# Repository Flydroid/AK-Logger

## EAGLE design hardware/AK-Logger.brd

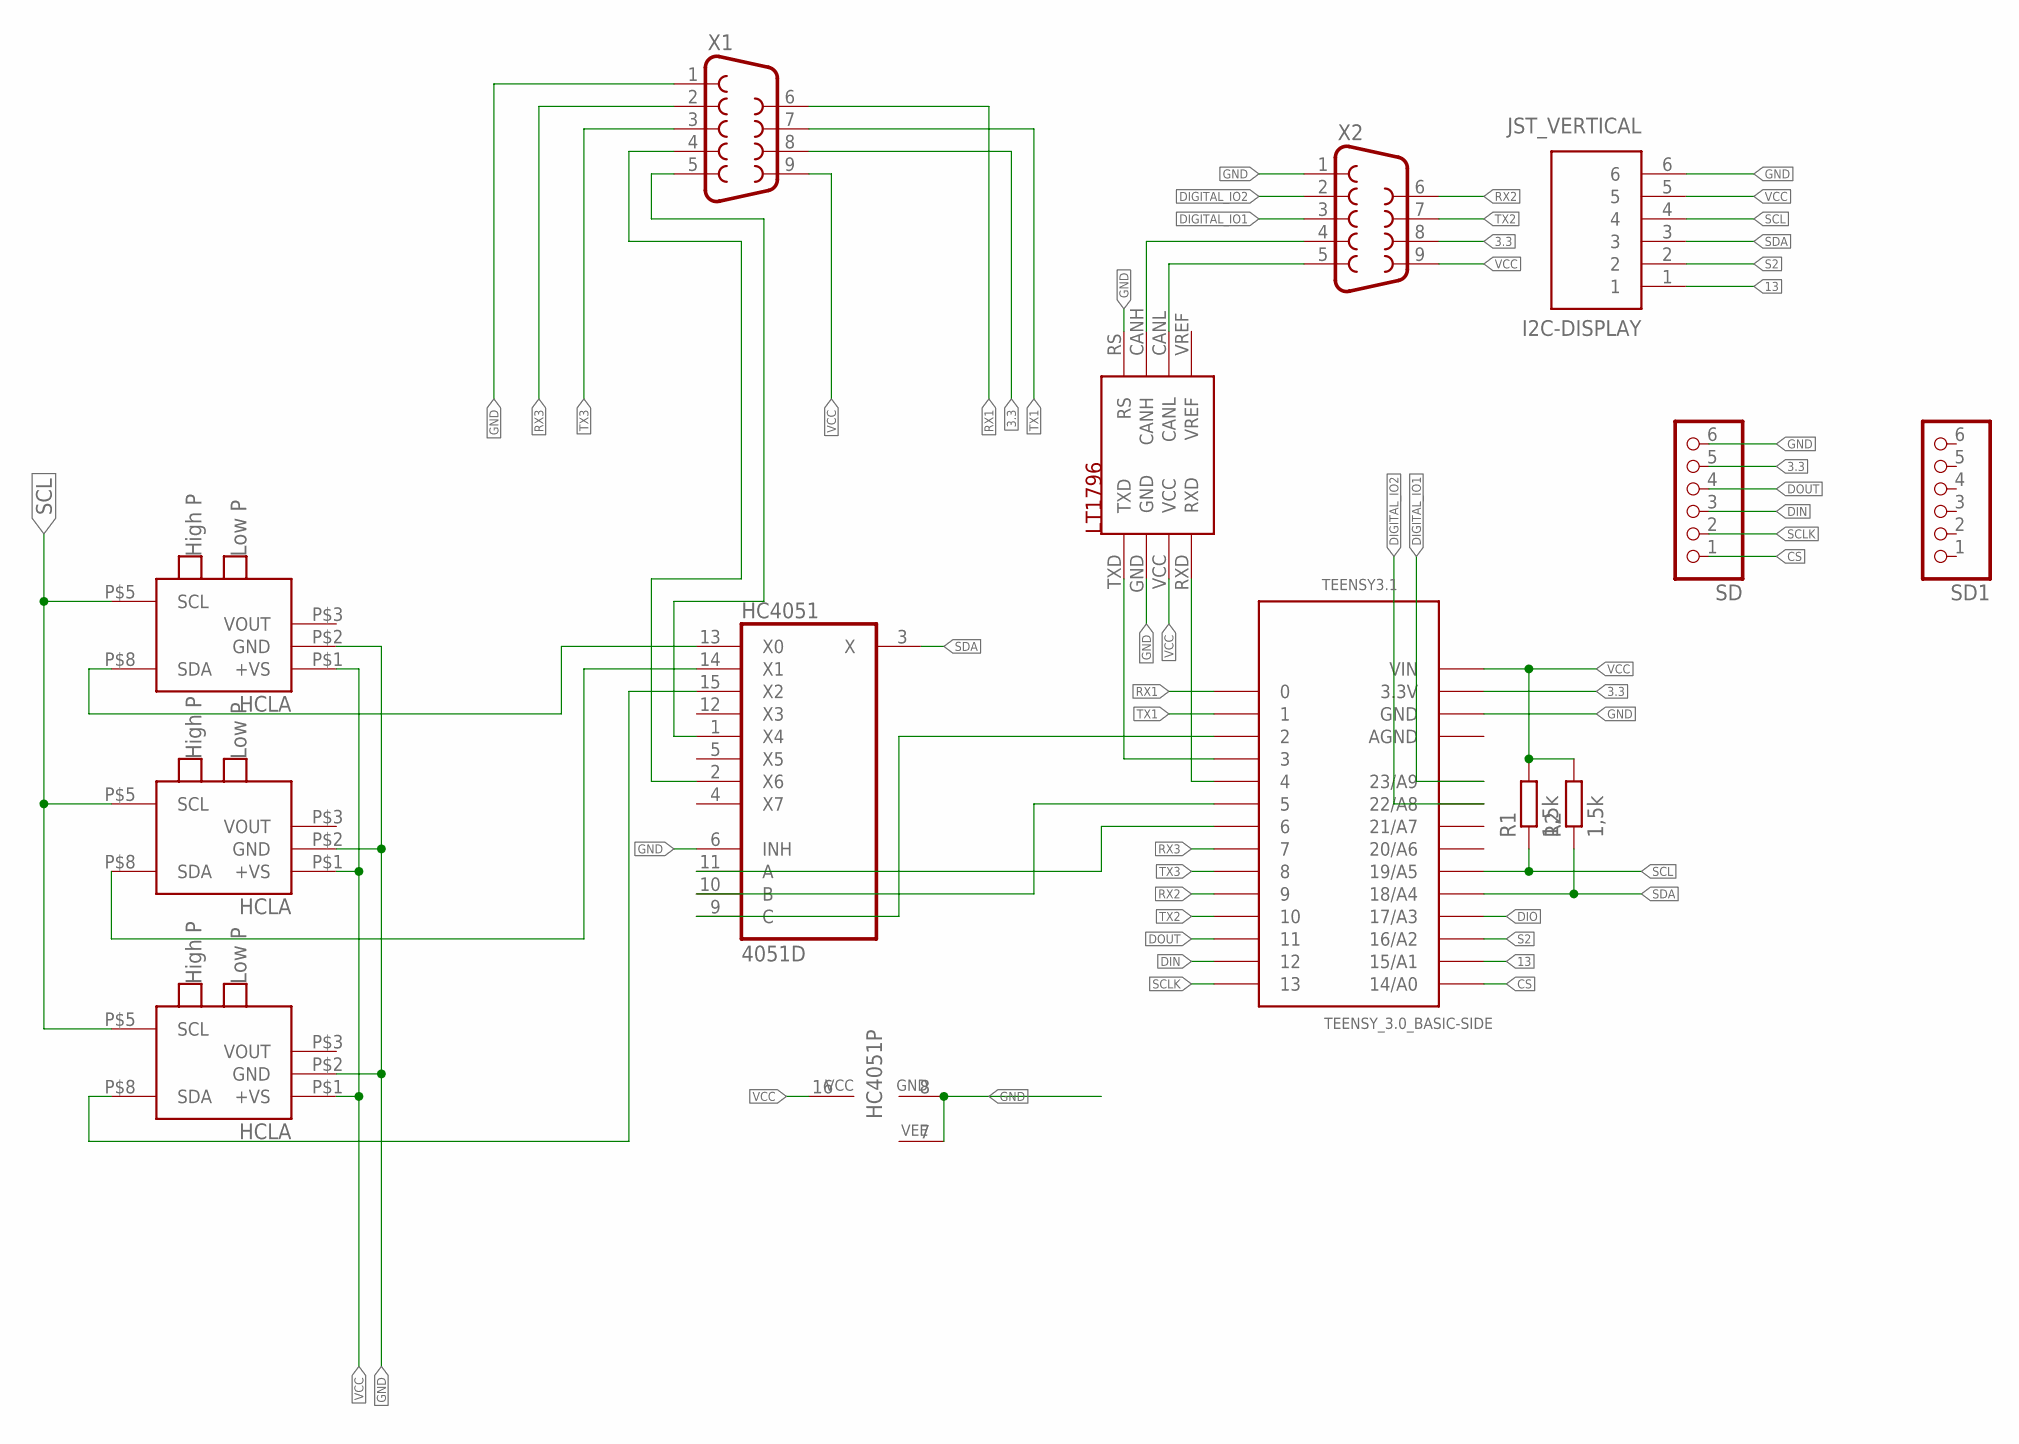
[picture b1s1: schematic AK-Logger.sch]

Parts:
HC4051: 4051D; SO16
HCLA0, HCLA1, HCLA2: HCLA
I2C-DISPLAY: JST_VERTICAL; JST-6-SMD-VERT-1.0MM
R1, R2: 1,5k; R1206
SD, SD1: PINHD-1X6; 1X06
TEENSY3.1: TEENSY_3.0_BASIC-SIDE
U$6: LT1796; SO08
X1, X2: F09H

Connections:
3.3: SD.5, TEENSY3.1.3.3V, X1.8, X2.8
13: I2C-DISPLAY.1, TEENSY3.1.15/A1
AGND: TEENSY3.1.AGND
CS: SD.1, TEENSY3.1.14/A0
DIGITAL_IO1: TEENSY3.1.23/A9, X2.3
DIGITAL_IO2: TEENSY3.1.22/A8, X2.2
DIN: SD.3, TEENSY3.1.12
DIO: TEENSY3.1.17/A3
DOUT: SD.4, TEENSY3.1.11
GND: HC4051.6 (INH), HC4051.7 (VEE), HC4051.8 (GND), HCLA0.P$2 (GND), HCLA1.P$2 (GND), HCLA2.P$2 (GND), I2C-DISPLAY.6, SD.6, TEENSY3.1.GND, U$6.GND, U$6.RS, X1.1, X2.1
unnamed: HC4051.14 (X1), HCLA1.P$8 (SDA)
unnamed: HC4051.13 (X0), HCLA0.P$8 (SDA)
unnamed: HC4051.15 (X2), HCLA2.P$8 (SDA)
unnamed: HC4051.10 (B), TEENSY3.1.5
unnamed: TEENSY3.1.3, U$6.TXD
unnamed: U$6.CANL, X2.5
unnamed: TEENSY3.1.4, U$6.RXD
unnamed: U$6.CANH, X2.4
unnamed: HC4051.11 (A), TEENSY3.1.6
unnamed: HC4051.9 (C), TEENSY3.1.2
unnamed: HC4051.1 (X4), X1.5
unnamed: HC4051.2 (X6), X1.4
RX1: TEENSY3.1.0, X1.6
RX2: TEENSY3.1.9, X2.6
RX3: TEENSY3.1.7, X1.2
S2: I2C-DISPLAY.2, TEENSY3.1.16/A2
SCL: HCLA0.P$5 (SCL), HCLA1.P$5 (SCL), HCLA2.P$5 (SCL), I2C-DISPLAY.4, R1.1, TEENSY3.1.19/A5
SCLK: SD.2, TEENSY3.1.13
SDA: HC4051.3 (X), I2C-DISPLAY.3, R2.1, TEENSY3.1.18/A4
TX1: TEENSY3.1.1, X1.7
TX2: TEENSY3.1.10, X2.7
TX3: TEENSY3.1.8, X1.3
VCC: HC4051.16 (VCC), HCLA0.P$1 (+VS), HCLA1.P$1 (+VS), HCLA2.P$1 (+VS), I2C-DISPLAY.5, R1.2, R2.2, TEENSY3.1.VIN, U$6.VCC, X1.9, X2.9

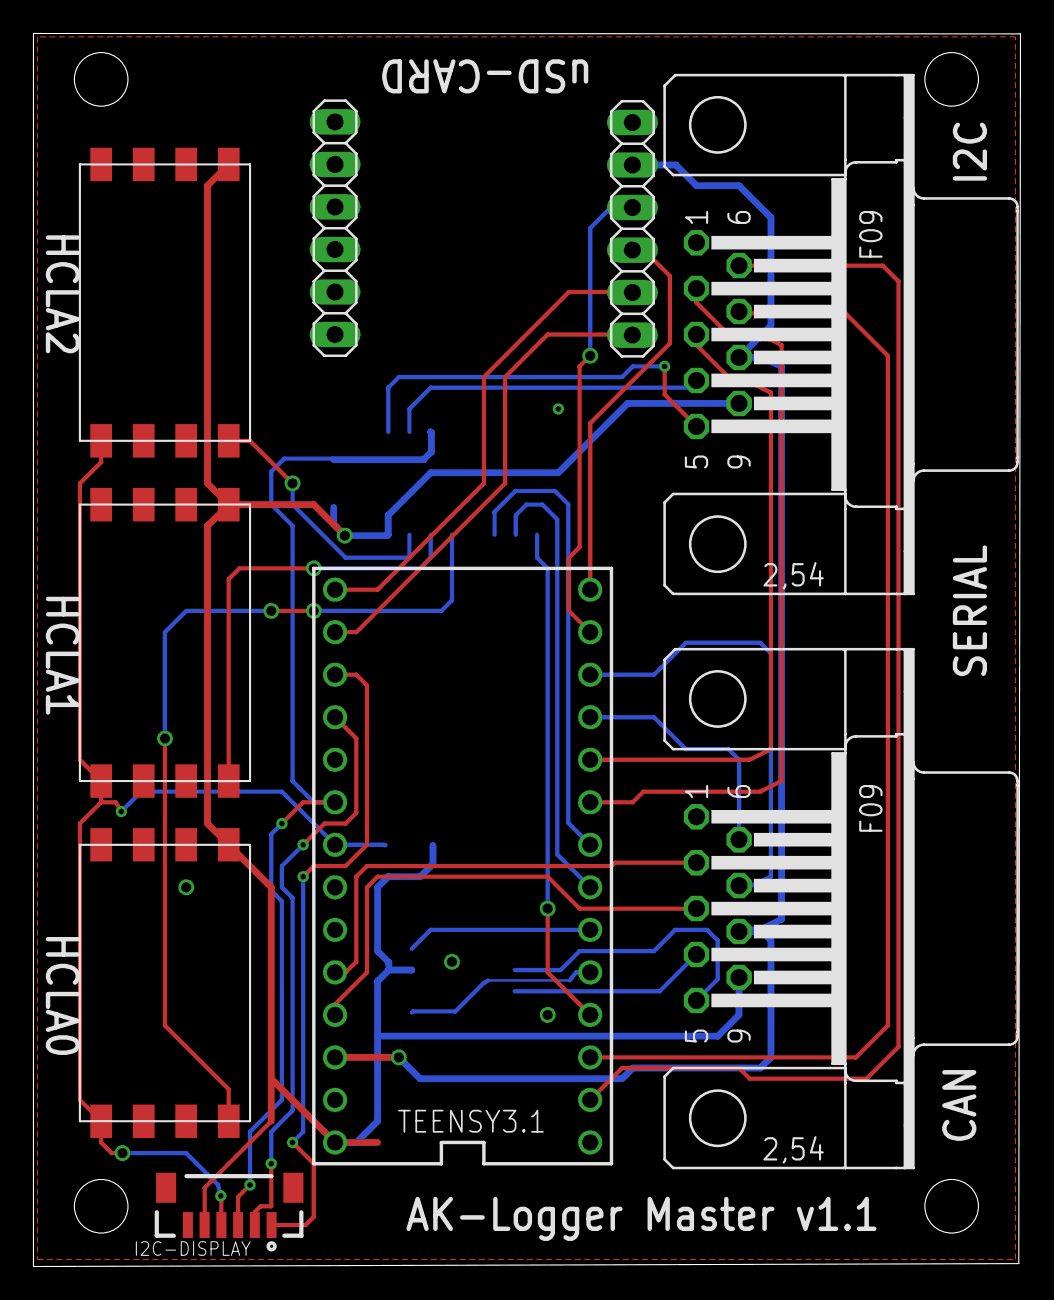
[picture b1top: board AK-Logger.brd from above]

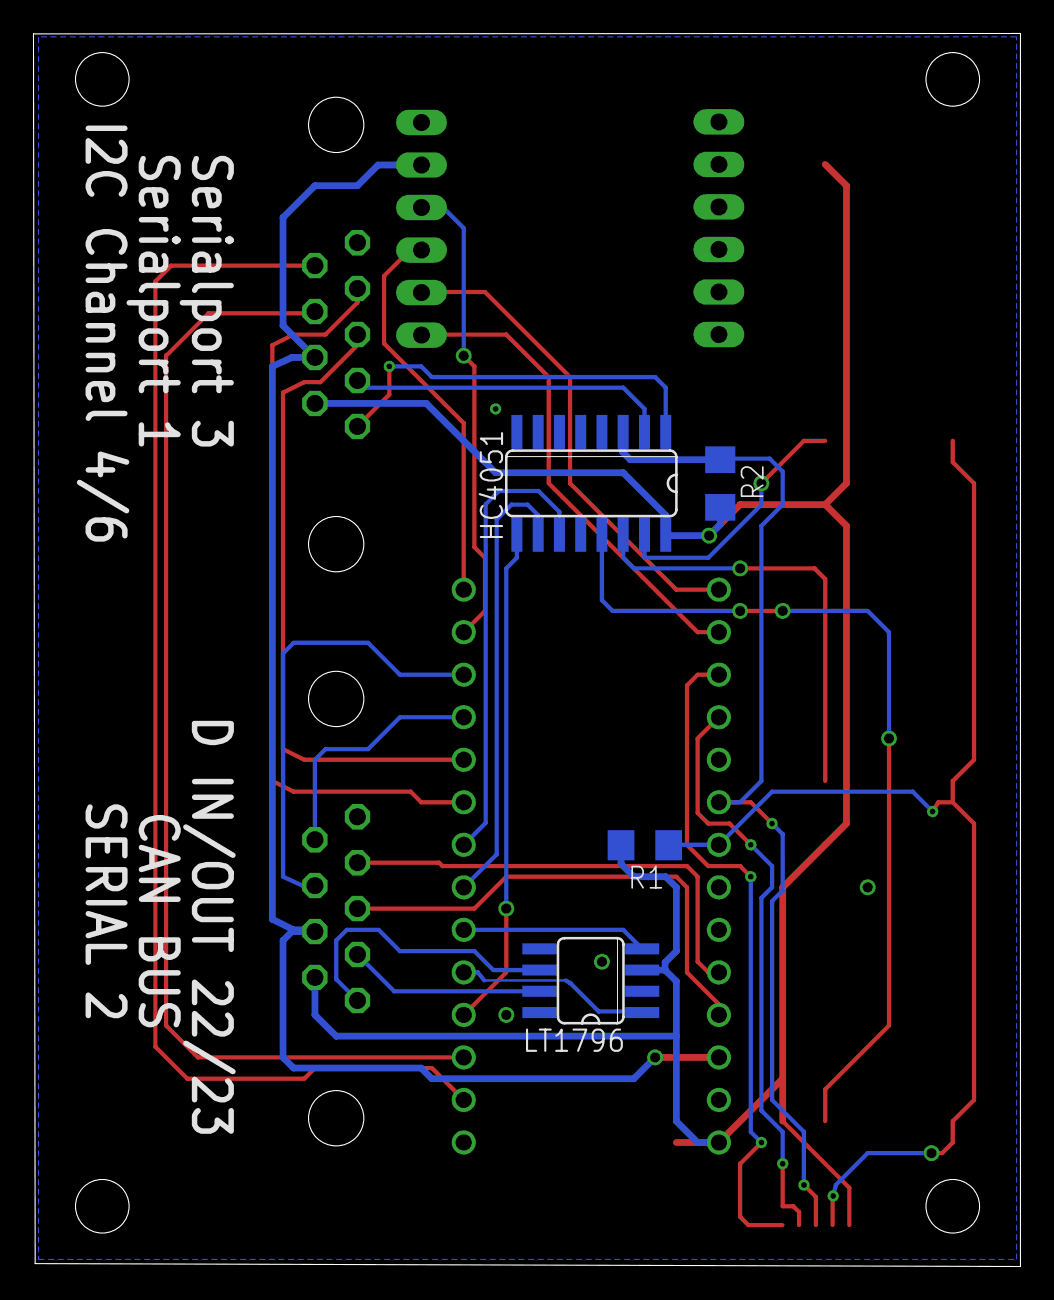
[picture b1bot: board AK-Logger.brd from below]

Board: 2 copper layers, 59.0 x 73.7 mm, 13 parts (4 on the bottom side), 31 nets.

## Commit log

2015-03-04 Initialisieren Sie das Commit, um ".gitIgnore"- und ".gitAttribute"-Standarddateien hinzuzufügen.
2015-03-04 Upload Basic Layout wurde erstellt HCLA lese funktion implementiert
2015-03-04 Klassen beschreibung hinzugefügt
2015-04-21 Mavlink: Airspeed und heartbeat
2015-04-26 gitupdate
2015-04-26 include fixed
2015-04-26 sdgdsgf
2015-04-27 Channelzuweisung, MAVLINK Fix, Messmodul mess und Senderoutine
2015-05-10 canbus logic - added struct for messmodul system state - added struct for handling the moduldata internal in the master -added checkin function for the messmodules during startup. ids, system state a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
2015-05-10 canbus logic update 2
2015-06-04 compile error fixed
2015-06-04 Name fix - removed from project name
2015-06-15 Keep it simple: save data on sd - format data to string and save it on the sd card - change module_data to vector
2015-06-23 Debug defines added, fixed channels memory allocation
2015-08-14 Master is working, SD card is working - removed compareModules funktion - removed all notions of mavlink.h - changed SD to sd, SD was probably a SdFat funktion - changed file open options to:O_RDWR |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
2015-11-04 Master update - 16 bit data container in module data - modul_data ist MAX_MODULES +1 groß -sd_file vs Serial option zum Debuggen ohne SD Card - Messmodul anmeldung cbus.read ist true dann werden Mess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
2015-11-09 added Time Managment
2015-11-11 Master update - added cout ArduinoOutStream with << - Filename Finder, finds a free filename - Save file cration time to to File - file creation time in header - save file change time to File - Time 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
2015-11-25 Modulupdate - Messmodul Identifikation im EEPROM des Moduls gespeichert
2016-03-25 Rename AKXLogger.ino to AKX-Logger.ino
2016-03-25 Module: - Module ID selection moved canbus: - write function as bool for better error control
2016-03-25 removed unused sdcard class
2016-03-25 fixed ino to match repo name
2016-03-25 platformio setup
2016-03-25 added schematic and layout files
2016-03-25 removed unnecessary libs
2016-03-25 platformio setup fixes
2016-03-25 platformio update platformio.vcxproj for Visualstudio project import
2016-04-09 Reorganized the old AK-X Logger code for the AK-Logger. - removed Master and Messmodule specific code - removed legacy feature code: Mavlink, Telemetry... - changed lib path to lib/LIBRARY - changed 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
2016-04-23 Start reorganizing code
2016-05-15 Create basic class structure
2016-05-15 Implement bare bones
2016-05-15 Make bare bones compileable
2016-05-15 Add SimpleList library
2016-05-15 Implement AKLogger class
2016-05-15 Implement ConsoleStream class
2016-05-15 Implement SensirionStream class
2016-05-15 Add line format functionality
2016-05-16 Make code compilable
2016-05-16 Fix minor bug
2016-05-22 Close streams properly on shutdown
2016-05-22 Update Sensirion pins
2016-05-22 Implement sdcard stream
2016-05-22 Improve error transparency
2016-05-22 Remove SDFat library
2016-05-22 Remove FlexCAN library
2016-05-22 Avoid overwriting existing files
2016-07-02 Fix automatic filename extension
2016-07-02 Add lx9000 stream classes
2016-07-02 Add TinyGPS lib
2016-07-02 Add methos stubs for lx9000 stream
2016-07-16 Implement Lx9000Stream
2016-08-28 Remove Lx9000 stream
2016-08-29 Add TimeStream class
2016-08-29 Integrate TimeStream
2016-08-29 Lower cpu speed
2016-09-06 Add time functionality
2016-09-06 Add Snooze library
2016-09-06 Remove snooze lib
2016-09-06 Add functionality to set time manually
2016-09-06 Update log format
2016-09-06 Remove old source files
2016-09-06 Remove time library
2016-09-06 Add time library
2016-09-06 Fix bugs
2016-09-06 Improve logging header
2016-09-09 Remove blocking calls
2016-09-09 Fix bugs and add functionality
2016-09-09 Change log file name
2016-09-09 Update log intervall
2016-09-09 Add python script to merge files
2016-09-09 Add script to generate random sensor files
2016-09-09 Finish script to generate sensor files
2016-09-09 Add example igc file
2016-09-09 Extend merge script
2016-09-09 Finish merge script
2016-09-09 Add altitude to logging merge data
2016-09-30 Kurrupte Datein ausgetauscht
2016-09-30 Kurrupte Datein ausgetauscht 2
2016-09-30 Kurrupte Datein ausgetauscht 3
2017-06-23 GPS Zeitsynchronisation
    untested
2017-07-05 Added GPS for time Sync, Added GPS for Logger Control - Working: Time Sync, start and stop of logger once - Buggy: Restart of Logger, wirting to sd card -> no files written
2017-07-06 GPS Time Working, Change to Sdfat Lib - Changed to SdFat lib because of the long file names. File creation and Logging is working - GPS Time Sync is working. - Restarting of streams still hangs
2017-07-14 fixed stream shutdown bug
2017-07-20 added Libs to platformio.ini
2017-07-20 deleted dependendy: String.h
2017-07-20 fixed timecheck added logger.start()
2017-07-31 GPS Baud fix Unterschiedliche Baudraten für DG1000 und ASG32
2017-11-29 Added AK-Logger.xml Board Pin Description

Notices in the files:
parts and their libraries:
SparkFun-Connectors: Licensing: Creative Commons ShareAlike 4.0 International - https://creativecommons.org/licenses/by-sa/4.0
